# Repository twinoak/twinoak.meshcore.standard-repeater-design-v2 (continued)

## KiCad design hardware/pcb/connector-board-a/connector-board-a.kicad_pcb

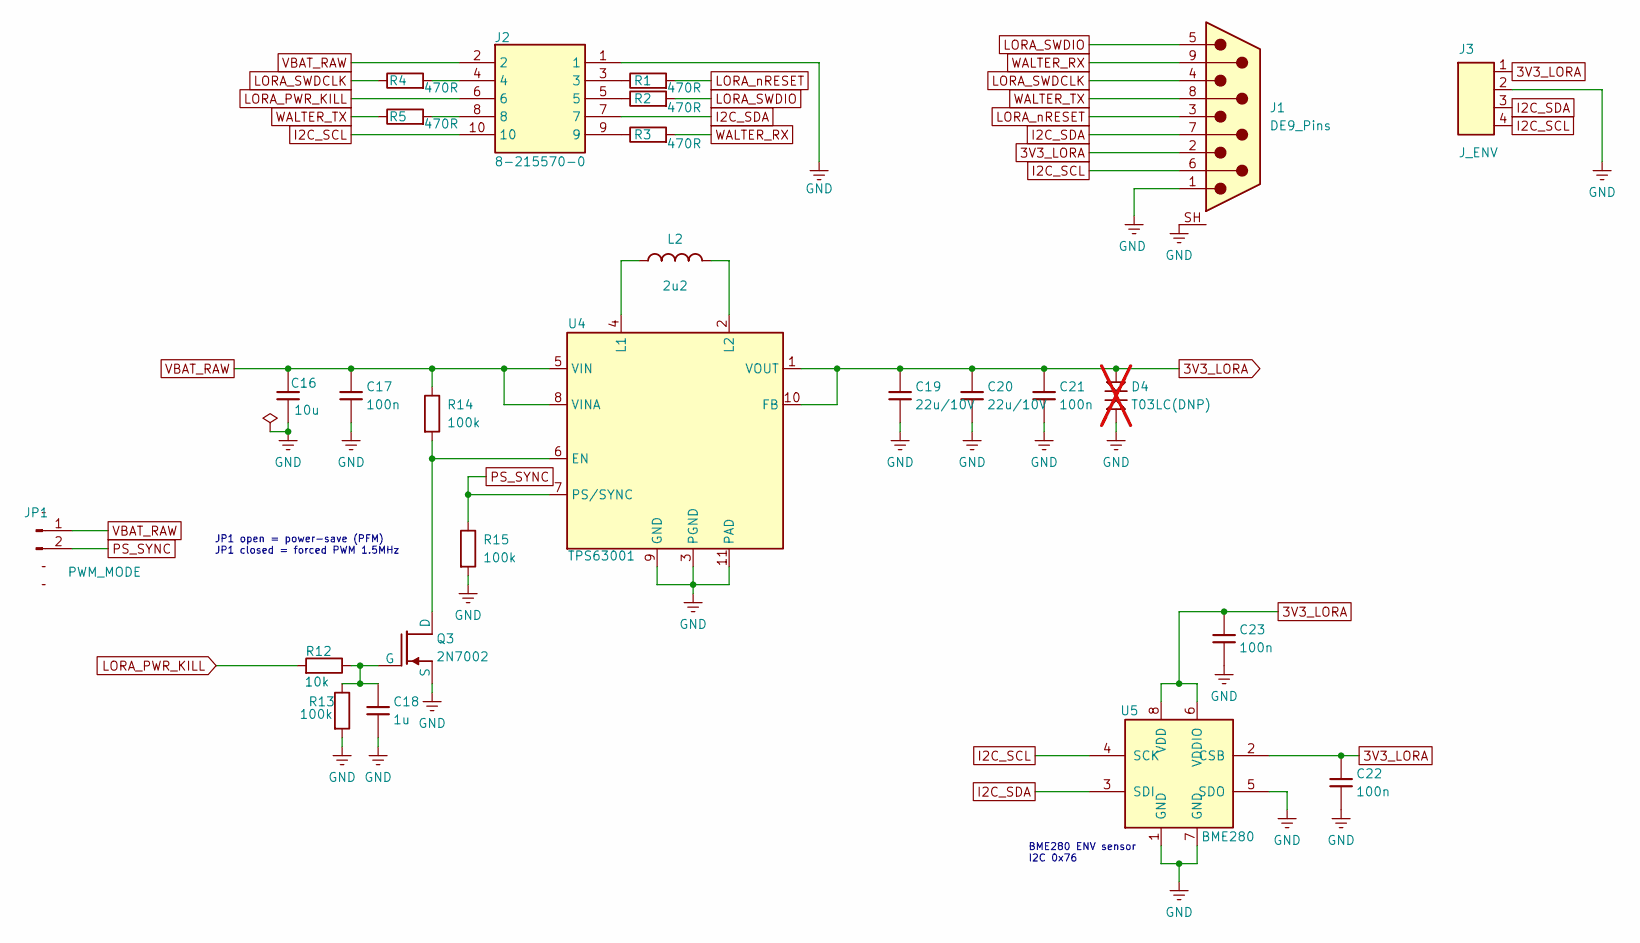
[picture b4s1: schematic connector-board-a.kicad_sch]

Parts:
C16: 10u; C_0805_2012Metric; LCSC Part # C15850
C17, C21, C22, C23: 100n; C_0603_1608Metric; LCSC Part # C14663
C18: 1u; C_0603_1608Metric; LCSC Part # C15849
C19, C20: 22u/10V; C_0805_2012Metric; LCSC Part # C45783
D4: T03LC(DNP); D_SOD-323; not fitted
J1: DE9_Pins; DSUB-9_Pins_Vertical_P2.77x2.84mm_MountingHoles
J2: 8-215570-0; 82155700; Manufacturer_Part_Number 8-215570-0
J3: J_ENV; PinHeader_1x04_P2.54mm_Vertical
JP1: PWM_MODE; PinHeader_1x02_P2.54mm_Vertical
L2: 2u2; L_Coilcraft_LPS4018; LCSC Part # C4354938
Q3: 2N7002; SOT-23; LCSC Part # C8545
R1, R2, R3, R4, R5: 470R; R_0805_2012Metric; LCSC Part # C17710
R12: 10k; R_0805_2012Metric; LCSC Part # C17414
R13, R14, R15: 100k; R_0805_2012Metric; LCSC Part # C149504
U4: TPS63001; Texas_DRC0010J; LCSC Part # C28060
U5: BME280; Bosch_LGA-8_2.5x2.5mm_P0.65mm_ClockwisePinNumbering; LCSC Part # C92489

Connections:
3V3_LORA: C19.1, C20.1, C21.1, C22.1, C23.1, D4.1, J1.2, J3.1, U4.1 (VOUT), U4.10 (FB), U5.2 (CSB), U5.6 (VDDIO), U5.8 (VDD)
GND: C16.2, C17.2, C18.2, C19.2, C20.2, C21.2, C22.2, C23.2, D4.2, J1.1, J1.SH, J2.1, J3.2, Q3.2 (S), R13.2, R15.2, U4.3 (PGND), U4.9 (GND), U4.11 (PAD), U5.1 (GND), U5.5 (SDO), U5.7 (GND)
I2C_SCL: J1.6, J2.10, J3.4, U5.4 (SCK)
I2C_SDA: J1.7, J2.7, J3.3, U5.3 (SDI)
LORA_PWR_KILL: J2.6, R12.1
LORA_SWDCLK: J1.4, R4.1
LORA_SWDIO: J1.5, R2.2
LORA_nRESET: J1.3, R1.2
unnamed: J2.3, R1.1
unnamed: J2.4, R4.2
unnamed: J2.5, R2.1
unnamed: J2.8, R5.2
unnamed: J2.9, R3.1
unnamed: Q3.3 (D), R14.2, U4.6 (EN)
unnamed: C18.1, Q3.1 (G), R12.2, R13.1
unnamed: L2.1, U4.4 (L1)
unnamed: L2.2, U4.2 (L2)
PS_SYNC: JP1.2, R15.1, U4.7 (PS/SYNC)
VBAT_RAW: C16.1, C17.1, J2.2, JP1.1, R14.1, U4.5 (VIN), U4.8 (VINA)
WALTER_RX: J1.9, R3.2
WALTER_TX: J1.8, R5.1

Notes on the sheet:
BME280 ENV sensor I2C 0x76
JP1 open = power-save (PFM) JP1 closed = forced PWM 1.5MHz

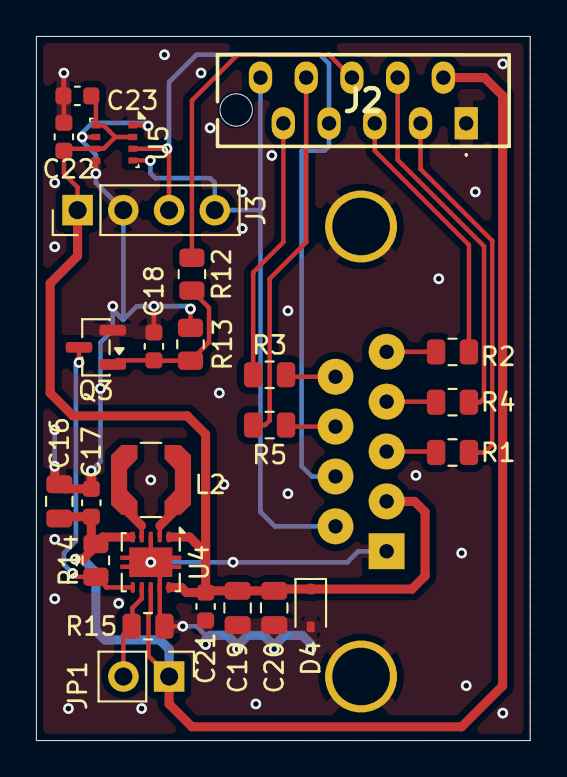
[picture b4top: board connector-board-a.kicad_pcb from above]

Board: 2 copper layers, 27.4 x 39.1 mm, 26 parts (1 on the bottom side), 21 nets.

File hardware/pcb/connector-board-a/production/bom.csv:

Designator,Footprint,Quantity,Value,LCSC Part #
C16,0805,1,10u,C15850
"C17, C21, C22, C23",0603,4,100n,C14663
C18,0603,1,1u,C15849
"C19, C20",0805,2,22u/10V,C45783
L2,L_Coilcraft_LPS4018,1,2u2,C4354938
Q3,SOT-23,1,2N7002,C8545
"R1, R2, R3, R4, R5",0805,5,470R,C17710
R12,0805,1,10k,C17414
"R13, R14, R15",0805,3,100k,C149504
U4,Texas_DRC0010J,1,TPS63001,C28060
U5,Bosch_LGA-8_2.5x2.5mm_P0.65mm_ClockwisePinNumbering,1,BME280,C92489

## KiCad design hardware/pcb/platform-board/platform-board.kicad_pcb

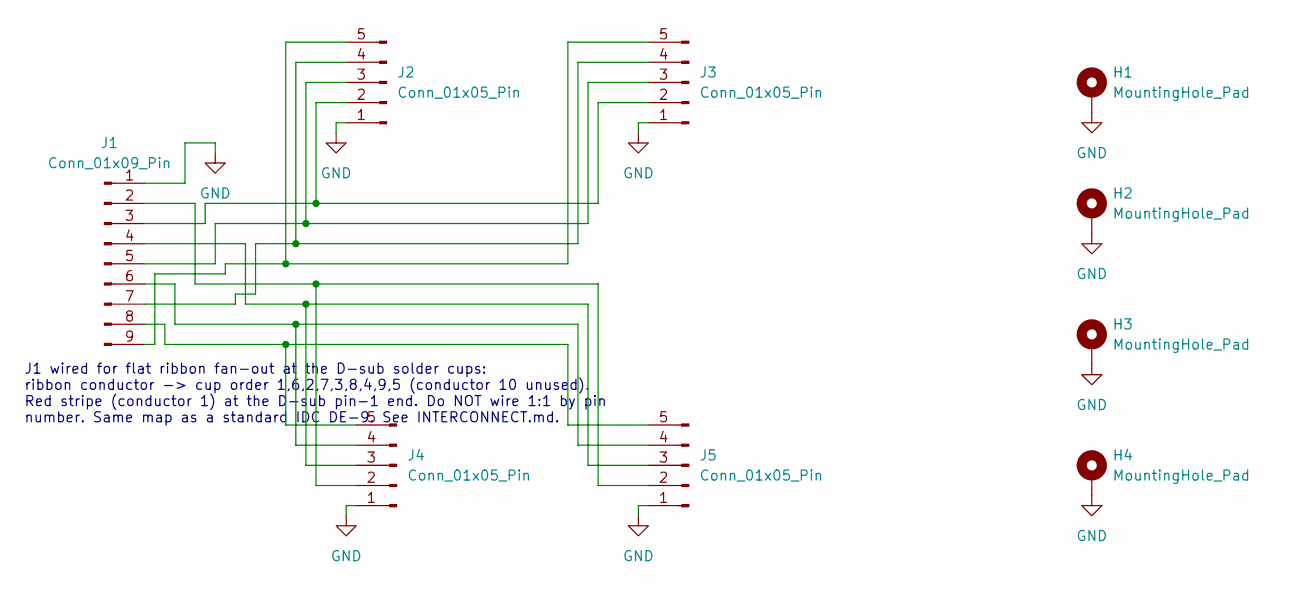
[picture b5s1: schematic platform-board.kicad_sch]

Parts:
H1, H2, H3, H4: MountingHole_Pad; MountingHole_3.5mm_Pad
J1: Conn_01x09_Pin; 82155700
J2, J3, J4, J5: Conn_01x05_Pin; PinHeader_1x05_P2.54mm_Vertical

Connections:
GND: H1.1 (1_1), H2.1 (1_1), H3.1 (1_1), H4.1 (1_1), J1.1, J2.1, J3.1, J4.1, J5.1
unnamed: J1.2, J4.2, J5.2
unnamed: J1.3, J2.2, J3.2
unnamed: J1.4, J4.3, J5.3
unnamed: J1.5, J2.3, J3.3
unnamed: J1.6, J4.4, J5.4
unnamed: J1.7, J2.4, J3.4
unnamed: J1.8, J4.5, J5.5
unnamed: J1.9, J2.5, J3.5

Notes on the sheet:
J1 wired for flat ribbon fan-out at the D-sub solder cups: ribbon conductor -> cup order 1,6,2,7,3,8,4,9,5 (conductor 10 unused). Red stripe (conductor 1) at the D-sub pin-1 end. Do NOT wire 1:1 by pin number. Same map as a standard IDC DE-9. See INTERCONNECT.md.

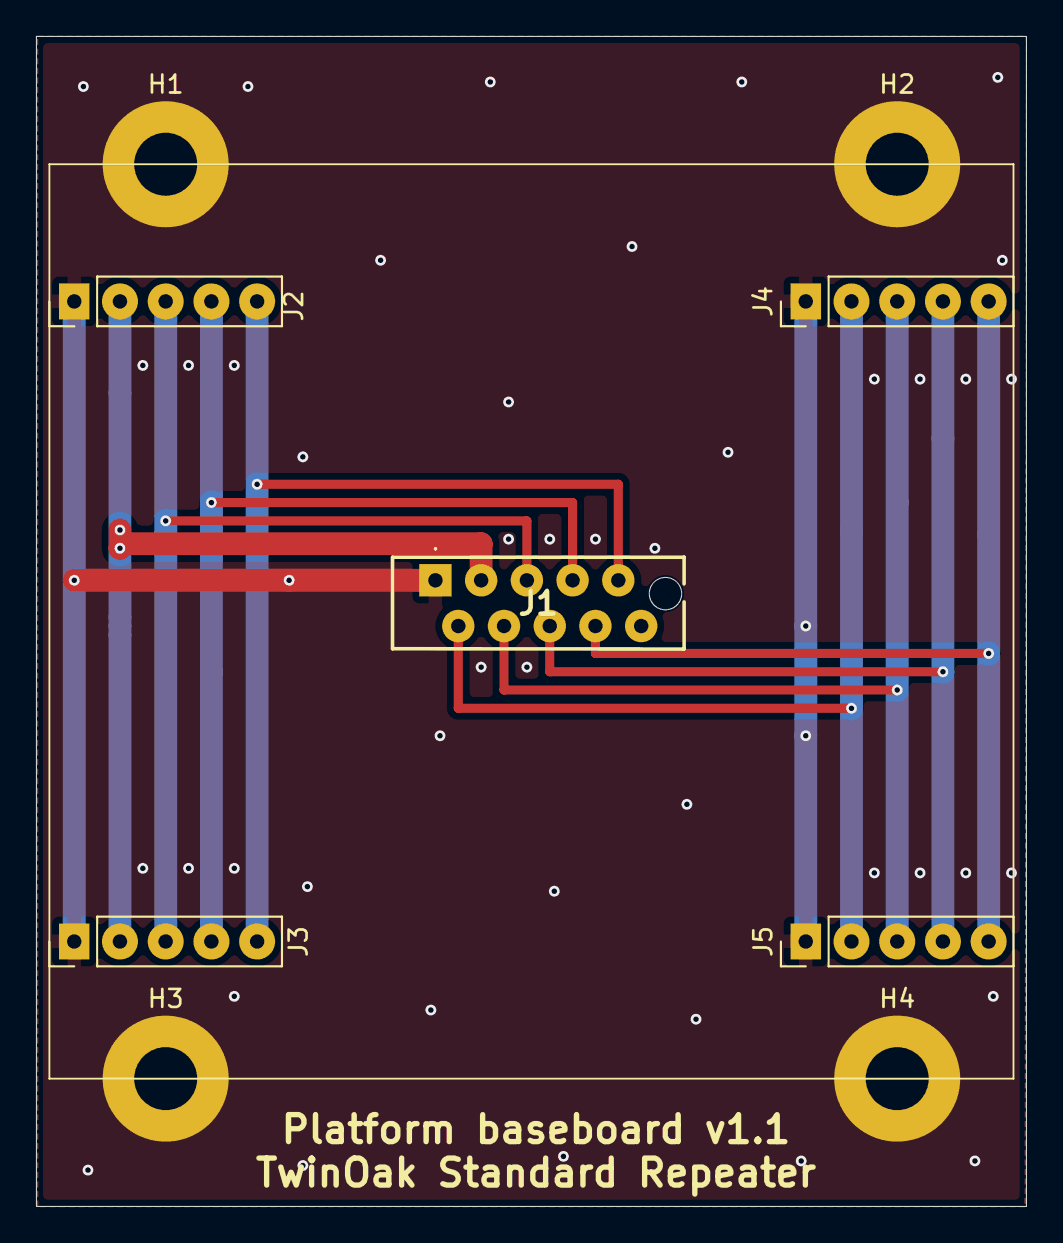
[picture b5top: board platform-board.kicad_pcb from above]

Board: 2 copper layers, 55.0 x 65.0 mm, 9 parts (0 on the bottom side), 9 nets.

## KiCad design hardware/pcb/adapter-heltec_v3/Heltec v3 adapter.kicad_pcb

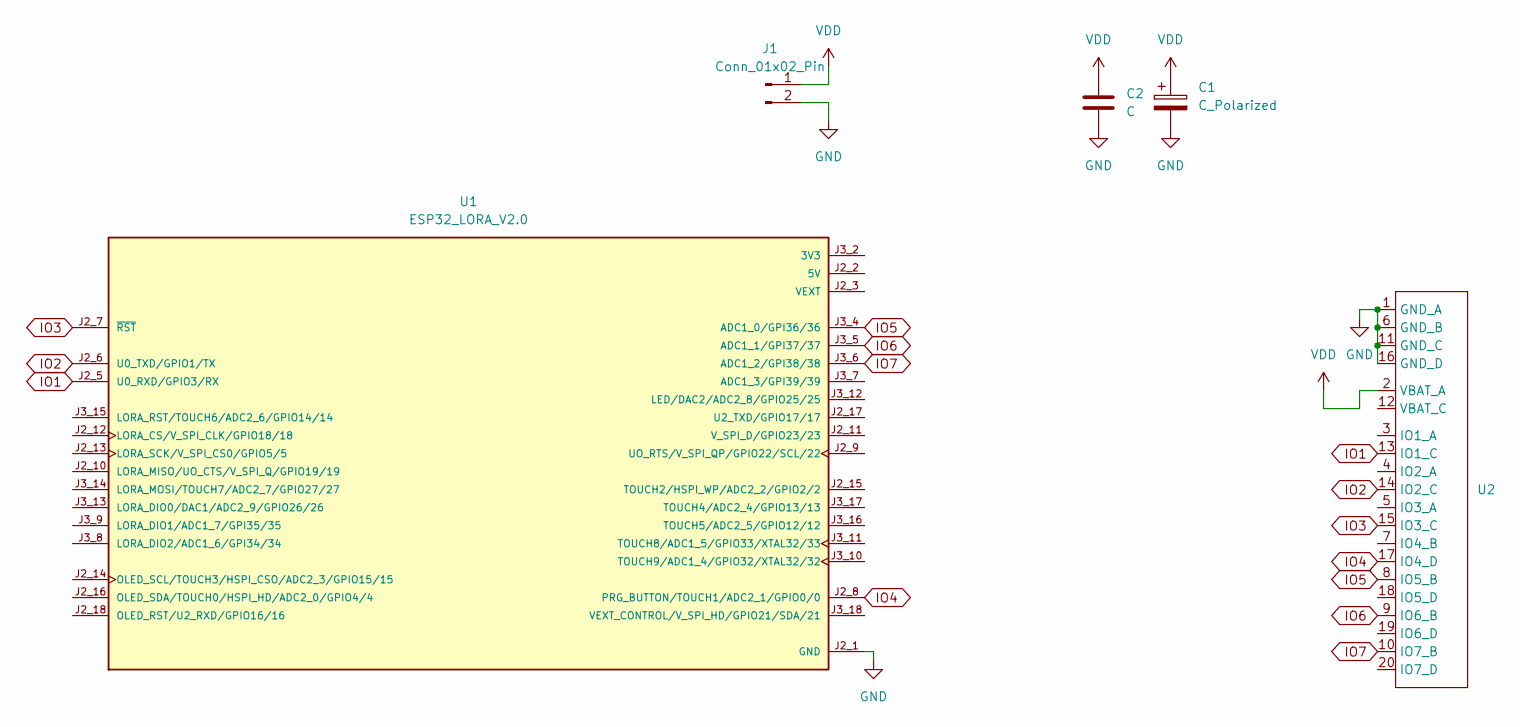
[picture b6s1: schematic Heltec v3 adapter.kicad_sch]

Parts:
C1: C_Polarized; CP_Radial_D8.0mm_P3.50mm
C2: C; C_Rect_L4.0mm_W2.5mm_P2.50mm
J1: Conn_01x02_Pin; PinHeader_1x02_P2.54mm_Vertical
U1: ESP32_LORA_V2.0; MODULE_ESP32_LORA_V2.0; PARTREV 2.0
U2: platform-adapter-footprint

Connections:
3V3: U1.J3_2 (3V3), U1.J3_3 (3V3)
GND: C1.2, C2.2, J1.2, U1.J2_1 (GND), U1.J3_1 (GND), U2.1 (GND_A), U2.6 (GND_B), U2.11 (GND_C), U2.16 (GND_D), U2.22, U2.23, U2.24, U2.25
IO1: U1.J2_5 (U0_RXD/GPIO3/RX), U2.13 (IO1_C)
IO2: U1.J2_6 (U0_TXD/GPIO1/TX), U2.14 (IO2_C)
IO3: U1.J2_7 (~RST), U2.15 (IO3_C)
IO4: U1.J2_8 (PRG_BUTTON/TOUCH1/ADC2_1/GPIO0/0), U2.17 (IO4_D)
IO5: U1.J3_4 (ADC1_0/GPI36/36), U2.8 (IO5_B)
IO6: U1.J3_5 (ADC1_1/GPI37/37), U2.9 (IO6_B)
IO7: U1.J3_6 (ADC1_2/GPI38/38), U2.10 (IO7_B)
VDD: C1.1, C2.1, J1.1, U2.2 (VBAT_A)
VEXT: U1.J2_3 (VEXT), U1.J2_4 (VEXT)

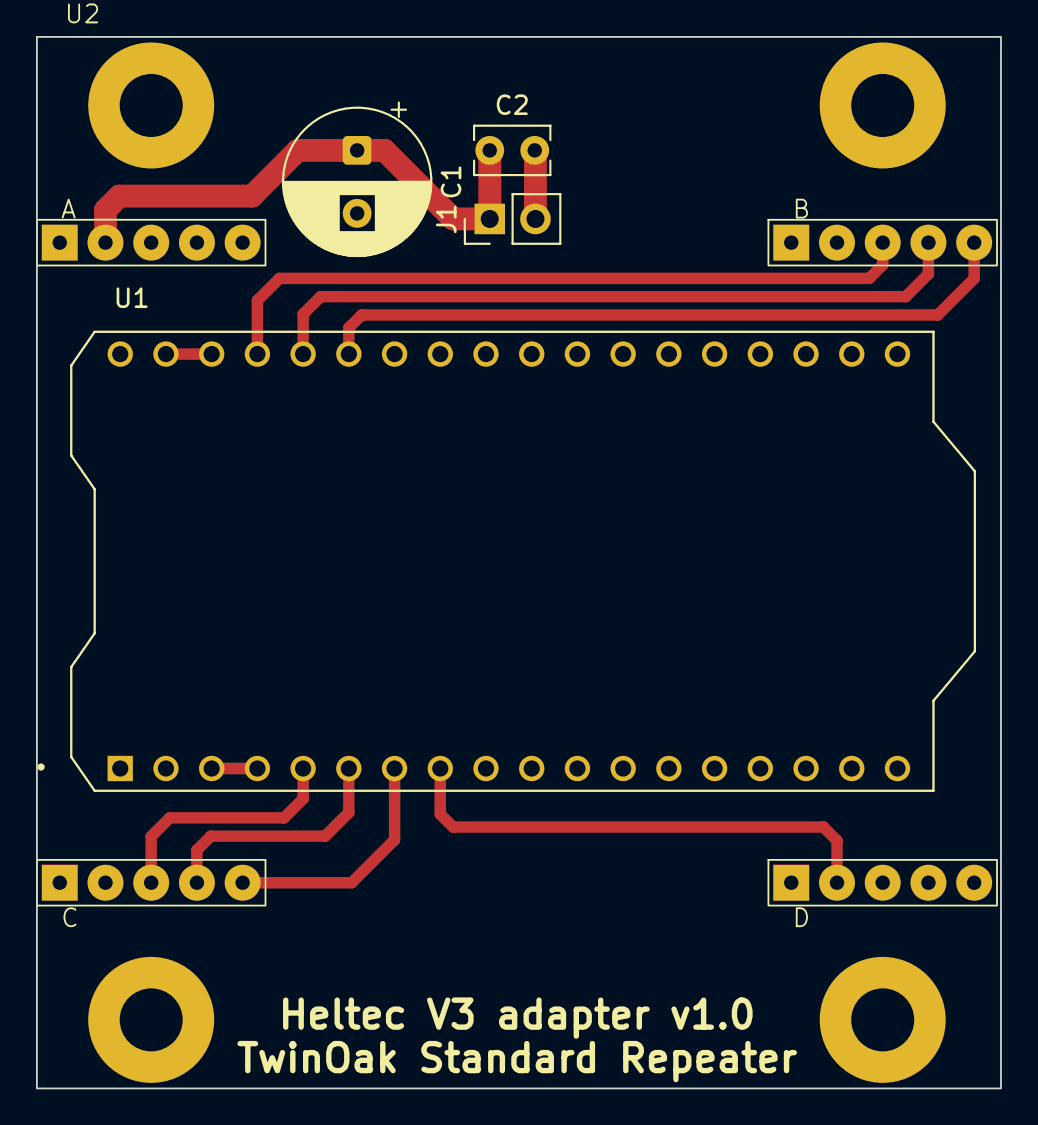
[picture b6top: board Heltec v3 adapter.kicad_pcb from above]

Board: 2 copper layers, 53.6 x 58.4 mm, 5 parts (0 on the bottom side), 11 nets.
